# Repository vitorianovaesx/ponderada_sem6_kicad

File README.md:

# Ponderada Semana 6 - Projeto no KiCad

Este repositório contém todos os arquivos de projeto necessários para a Ponderada Sem 6, incluindo esquemático, layout de PCB e os arquivos Gerber para fabricação.

## Estrutura do diretório
`ponderadasem6_kicad`: Diretório raiz do projeto KiCad.

`ponderada_sem6_kicad_backups`: Contém arquivos de backup para o projeto.

`gerbers`: Pasta que contém os arquivos Gerber necessários para a fabricação da PCB. Isso inclui camadas de cobre, camadas de máscara, serigrafia e cortes de borda e são os arquivos com final .gbr.

`schematic (esquemático)`: O layout esquemático do Ponderada Sem 6 está dentro do arquivo .sch.

`pcb`: O projeto da PCB pode ser acessado com o arquivo .kicad_pcb.

## Árvore de arquivos :
```
├── ponderadasem6_kicad
│   ├── ponderada_sem6_kicad-backups
│   ├── ponderada_sem6_kicad-B_Cu.gbr
│   ├── ponderada_sem6_kicad-B_Mask.gbr
│   ├── ponderada_sem6_kicad-B_Paste.gbr
│   ├── ponderada_sem6_kicad-B_Silkscreen.gbr
│   ├── ponderada_sem6_kicad-Edge_Cuts.gbr
│   ├── ponderada_sem6_kicad-F_Cu.gbr
│   ├── ponderada_sem6_kicad-F_Mask.gbr
│   ├── ponderada_sem6_kicad-F_Paste.gbr
│   ├── ponderada_sem6_kicad-F_Silkscreen.gbr
│   ├── ponderada_sem6_kicad-job.gbrjob
│   ├── ponderada_sem6_kicad.kicad_pcb
│   ├── ponderada_sem6_kicad.kicad_prl
│   ├── ponderada_sem6_kicad.kicad_pro
│   ├── ponderada_sem6_kicad.kicad_sch

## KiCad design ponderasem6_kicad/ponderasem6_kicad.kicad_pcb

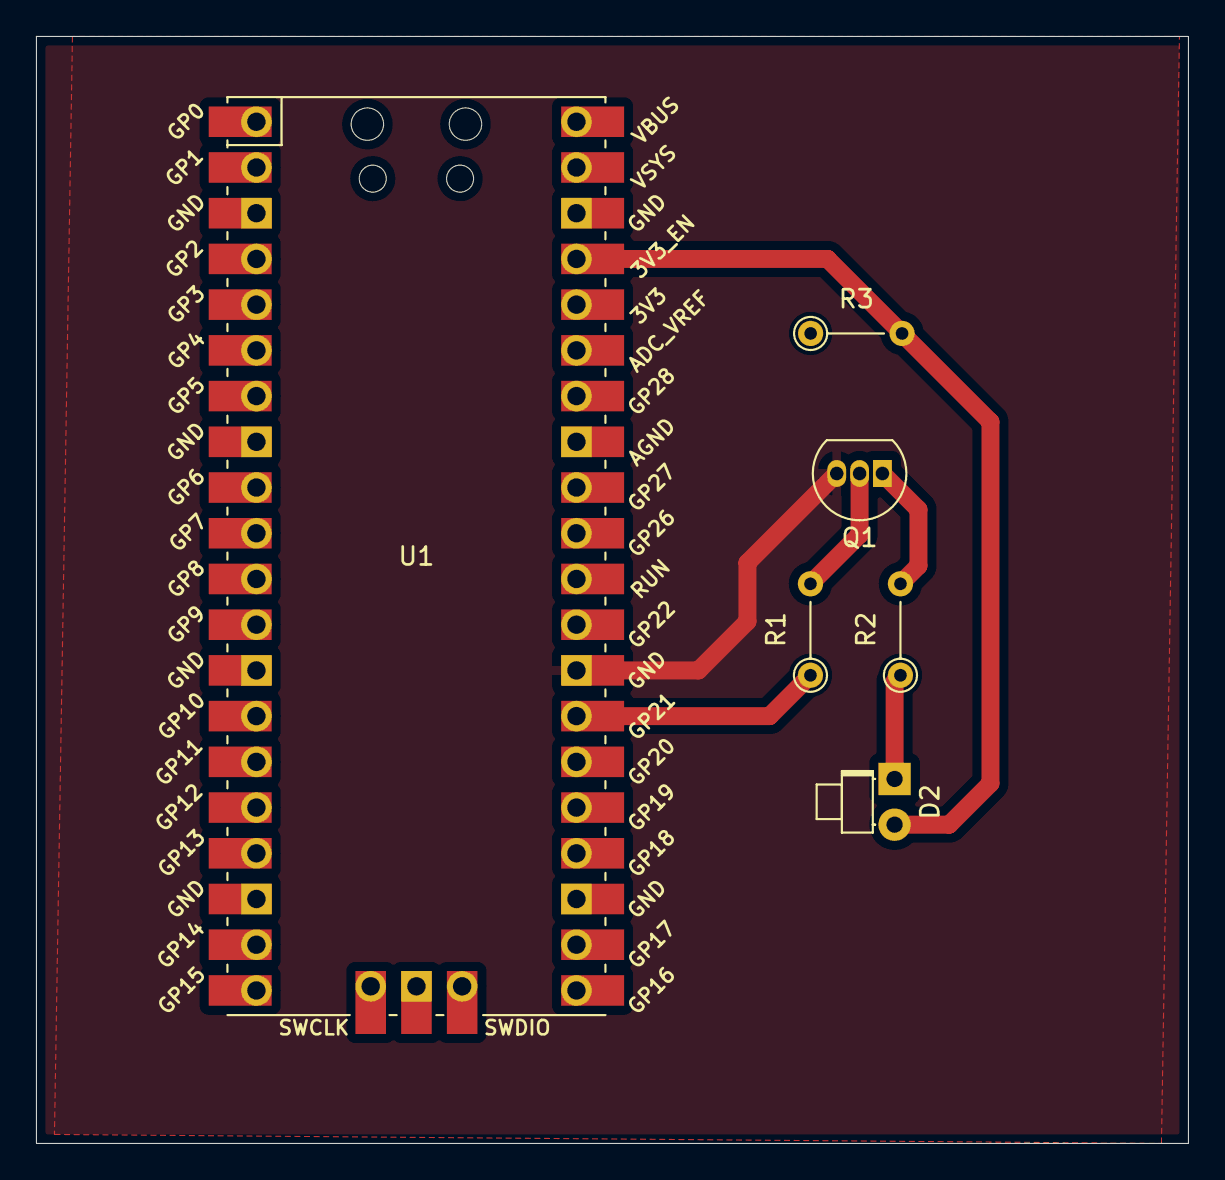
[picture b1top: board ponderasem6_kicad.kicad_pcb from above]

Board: 2 copper layers, 64.0 x 61.5 mm, 6 parts (0 on the bottom side), 6 nets.

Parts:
D2: LED; LED_D1.8mm_W1.8mm_H2.4mm_Horizontal_O1.27mm_Z8.2mm
Q1: BC548; TO-92_Inline
R1: 10K; R_Axial_DIN0204_L3.6mm_D1.6mm_P5.08mm_Vertical
R2, R3: 220; R_Axial_DIN0204_L3.6mm_D1.6mm_P5.08mm_Vertical
U1: Pico; RPi_Pico_SMD_TH

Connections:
3v3: D2.2 (A), R3.2, U1.37 (3V3_EN)
GND: Q1.3 (E), U1.28 (GND)
unnamed: D2.1 (K), R2.1
unnamed: Q1.2 (B), R1.2
unnamed: Q1.1 (C), R2.2
unnamed: R1.1, U1.27 (GPIO21)

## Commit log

2024-03-28 gerbers, schematic and pcb board
2024-03-28 atualização de arquivos
2024-03-28 atualização de arquivos 2
